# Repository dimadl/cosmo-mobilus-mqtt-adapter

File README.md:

# COSMO Mobilus shutters x Home Assistant (MQTT) Adapter
This repository provides all the necessary information—both software and hardware—to build your own adapter that connects COSMO Mobilus-controlled shutters to Home Assistant via MQTT.

The hardware setup is based on an actual COSMO Mobilus remote control and requires basic soldering skills to complete.

A high-level schematic of the end-to-end solution is shown in the diagram below.

## Motivation
There is no native support for COSMO protocol in Home Assistant.

## Features
- [x] Each shutter is automatically discovered by Home Assistant.
- [x] Position control is supported for each shutter, where 100 represents fully open and 0 fully closed.
- [x] Shutter positions are stored in memory to prevent re-synchronization after restarts.
- [x] The current position of the remote control unit is also saved in memory.

## Schematic

## Supported Device
- Mobilus COSMO HM
- Mobilus COSMO HM1
- Mobilus COSMO HM3+
- Mobilus COSMO G3+ Light (*)
- Mobilus COSMO WM (*)
- Mobilus COSMO L5 (*)
- Mobilus COSMO L1 (*)

(*) - These devices have not been tested; however, given that they use mechanical switches, this approach is expected to work with them as well.

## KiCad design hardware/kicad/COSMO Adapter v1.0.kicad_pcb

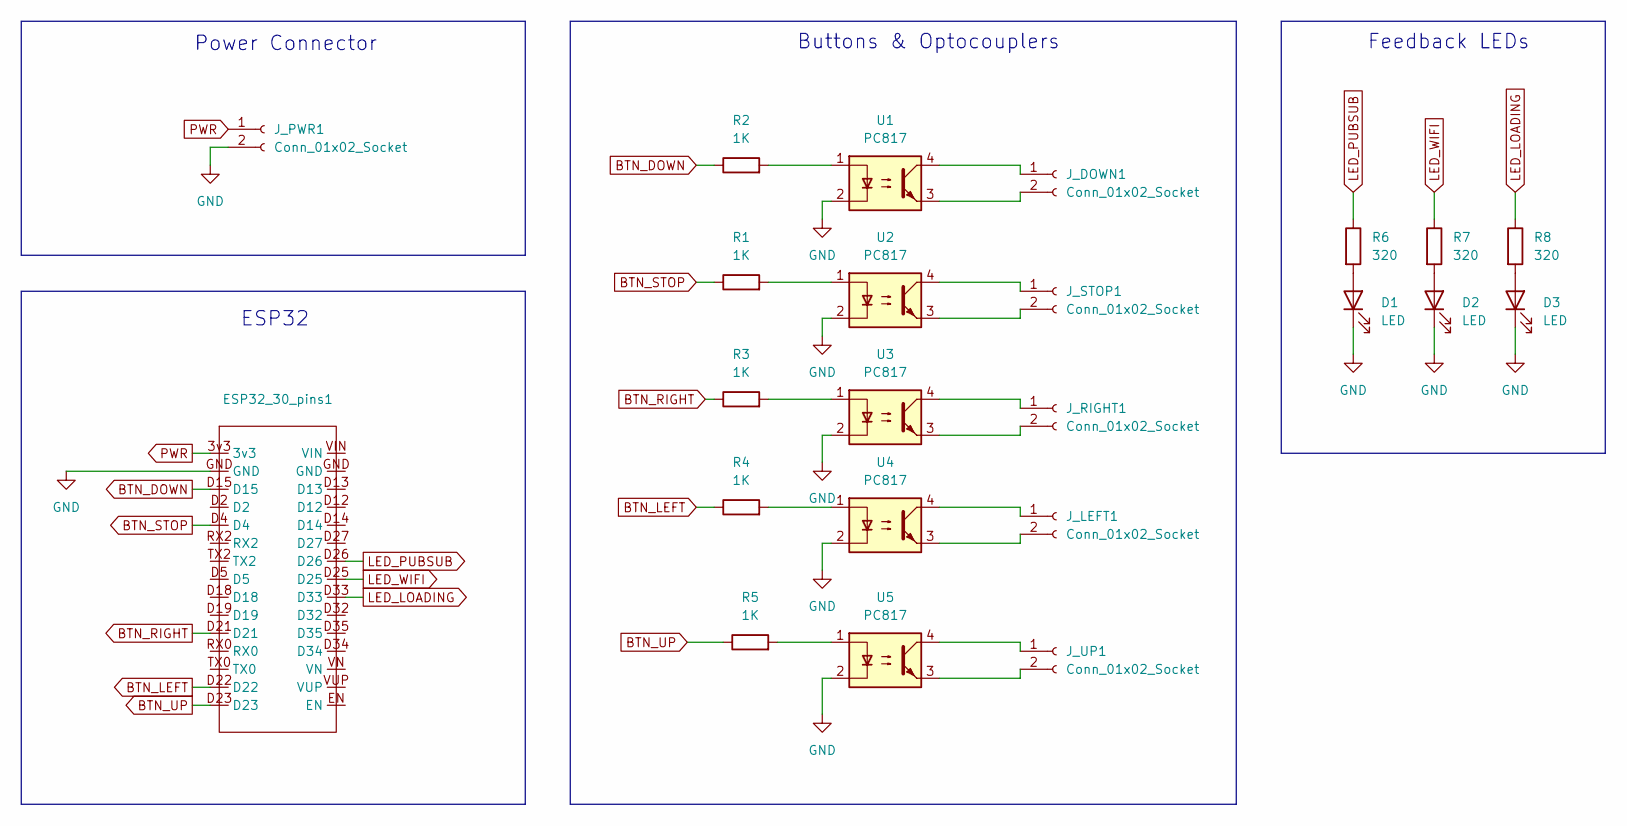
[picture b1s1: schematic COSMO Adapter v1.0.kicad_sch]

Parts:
D1, D2, D3: LED; LED_D3.0mm
ESP32_30_pins1: ESP_32_DevKit_30
J_DOWN1: Conn_01x02_Socket; PinHeader_1x02_P2.54mm_Vertical
J_LEFT1: Conn_01x02_Socket; PinHeader_1x02_P2.54mm_Vertical
J_PWR1: Conn_01x02_Socket; PinHeader_1x02_P2.54mm_Vertical
J_RIGHT1: Conn_01x02_Socket; PinHeader_1x02_P2.54mm_Vertical
J_STOP1: Conn_01x02_Socket; PinHeader_1x02_P2.54mm_Vertical
J_UP1: Conn_01x02_Socket; PinHeader_1x02_P2.54mm_Vertical
R1, R2, R3, R4, R5: 1K; R_Axial_DIN0207_L6.3mm_D2.5mm_P7.62mm_Horizontal
R6, R7, R8: 320; R_Axial_DIN0207_L6.3mm_D2.5mm_P7.62mm_Horizontal
U1, U2, U3, U4, U5: PC817; DIP-4_W7.62mm

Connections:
BTN_DOWN: ESP32_30_pins1.D15, R2.1
BTN_LEFT: ESP32_30_pins1.D22, R4.1
BTN_RIGHT: ESP32_30_pins1.D21, R3.1
BTN_STOP: ESP32_30_pins1.D4, R1.1
BTN_UP: ESP32_30_pins1.D23, R5.1
GND: D1.1 (K), D2.1 (K), D3.1 (K), ESP32_30_pins1.GND, J_PWR1.2, U1.2, U2.2, U3.2, U4.2, U5.2
LED_LOADING: ESP32_30_pins1.D33, R8.1
LED_PUBSUB: ESP32_30_pins1.D26, R6.1
LED_WIFI: ESP32_30_pins1.D25, R7.1
unnamed: D1.2 (A), R6.2
unnamed: D2.2 (A), R7.2
unnamed: D3.2 (A), R8.2
unnamed: J_DOWN1.1, U1.4
unnamed: J_DOWN1.2, U1.3
unnamed: J_LEFT1.1, U4.4
unnamed: J_LEFT1.2, U4.3
unnamed: J_RIGHT1.1, U3.4
unnamed: J_RIGHT1.2, U3.3
unnamed: J_STOP1.1, U2.4
unnamed: J_STOP1.2, U2.3
unnamed: J_UP1.1, U5.4
unnamed: J_UP1.2, U5.3
unnamed: R1.2, U2.1
unnamed: R2.2, U1.1
unnamed: R3.2, U3.1
unnamed: R4.2, U4.1
unnamed: R5.2, U5.1
PWR: ESP32_30_pins1.3v3, J_PWR1.1

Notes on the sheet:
ESP32
Feedback LEDs
Power Connector
Buttons & Optocouplers

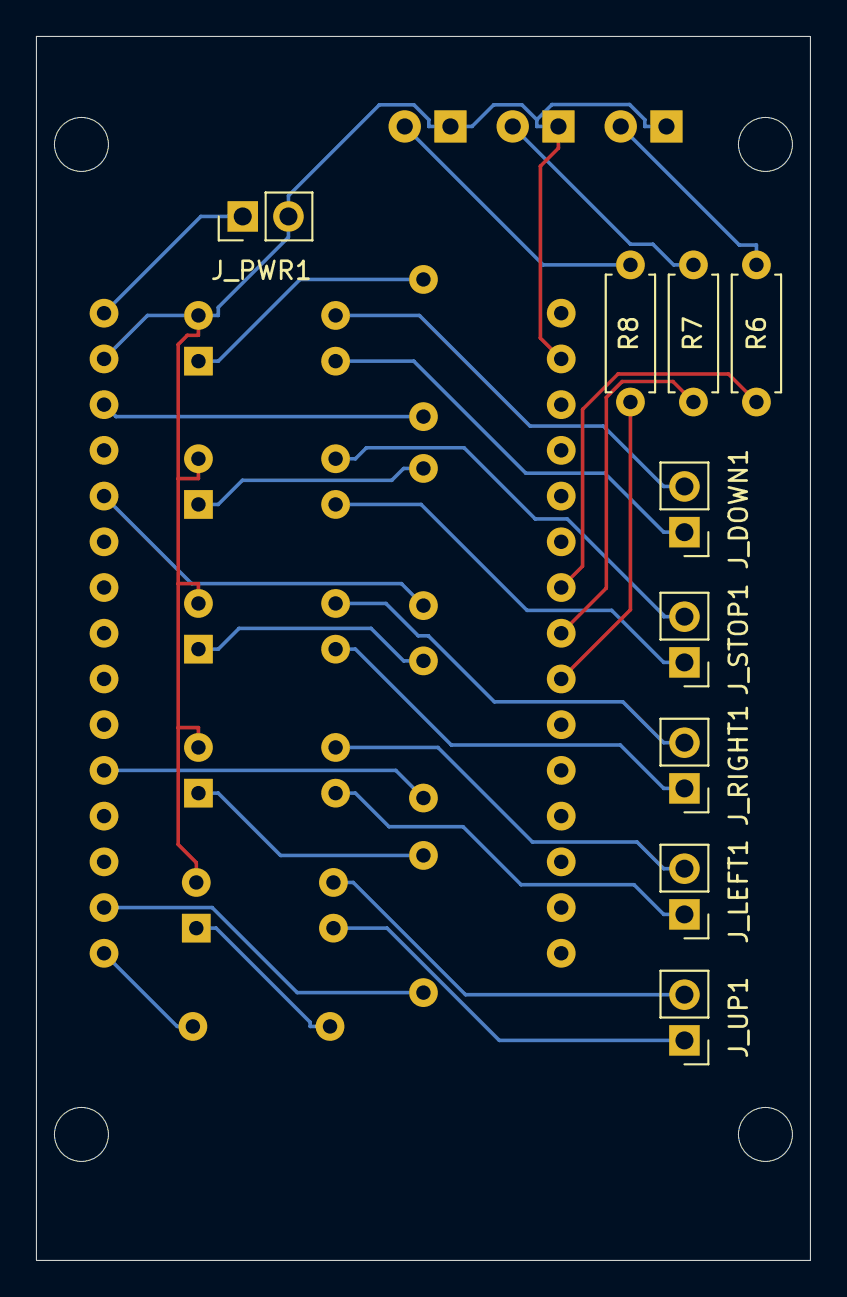
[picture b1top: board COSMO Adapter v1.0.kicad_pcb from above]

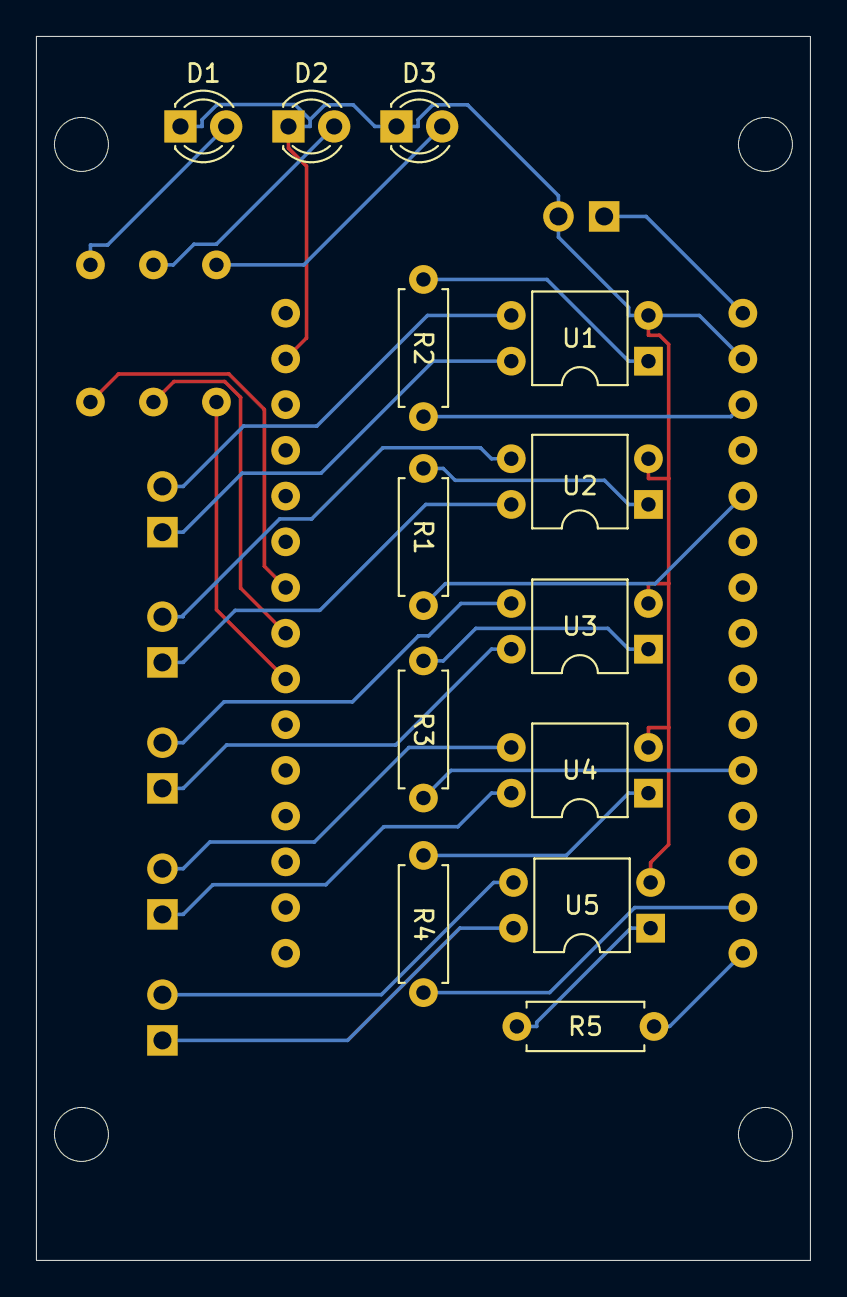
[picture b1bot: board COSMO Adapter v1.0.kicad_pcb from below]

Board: 2 copper layers, 43.0 x 68.0 mm, 23 parts (13 on the bottom side), 28 nets.

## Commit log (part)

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2025-08-03 Starts a project to integrate Cosmo Mobilus shutters with Home Assistant via MQTT protocol
2025-08-03 Adds MQTT support and integration with Home Assistant
    - Enables device discovery in Home Assistant
    - Implements simple callback for the command coming from the HA
    - Starts global refactorings to enable scaling up to several switches
2025-08-07 Adds new abstraction for the shutters
    - Implements HAMQTTShutter as a primary abstraction representing shutters
    - Unifies the way all shutter will send deiscovery message to Home Assistant via MQTT
2025-08-08 Iinitializes the controller abstraction
    - Adds a new abstraction HAMQTTShutterControl that will be controlling assigned shutters
    - Adds initialization of the registered shutters through the HAMQTTShutterControl
2025-08-09 Prepares the integration to receive commands from MQTT
    - Makes the shutter devices available for setting possition through automatios in Home Assistant
    - Every shutter subscribe to commands from Home Assistant (open, close, stop)
    - Pins initializtion for future optocouplers
2025-08-09 Implements a logic to set positions for the required shutter
    - Adds methods to manipulate the shutter (open, close, stop) based on the requested position
2025-08-09 Add abstraction for the hardware of Cosmo Mobilus HM control
2025-08-10 Fixed the issue with topics
2025-08-10 Added availability state sending
2025-08-10 Fixed the issue with positioning the current shutter on the control
2025-08-10 Refactors manipulation functions using pointers to the shutter
    - Repalces the array lookup with pointers to the shutter in the manupulation functions
2025-08-10 Adds "opened" and "closing" states to the shutter to report.
    - Home Assistant allows to have deterministic states for the shutter (opened, opening, closed, closing, stopped)
    - Adds report functions accordingly
2025-08-20 The first integration with real hardware.
    - Fixed few issues related to button press delays
    - Fixed an issue with moving counter on the hardware forward and backward (added delay to the button)
2025-08-20 Changed the size of EEPROM and moved current control position initisalization to the begin()
2025-08-21 Implements MQTT Client with fault tolerance and resilience
    - Implements rproxy for PubSubClient
    - Proxies "subscribe()" method with retry policies
    - Proxies "publish()" method with retru policies
2025-08-21 Refactors the proxy for MQTTClient
    - Moves MQTT broker initializtion to new proxy client
    - Moves callback inside of HAMQTTShutterControl
2025-08-24 Implements vfeedback on what's happenning inside
    - Adds a strategy that delegates feedback methods to LEDs.
    - Adds a onConnected callback for the MQTTClient. It can be usded to react re-connecrtion. The plan is to re-subscribe when a re-connection happened
2025-08-30 Adds README file with a description
2025-09-03 Replaces configuration with user inputs
    - Uses WifiManager to connect to wifi and as manager for MQTT configuration
    - Refactores main.cpp according to the latest changes
2025-09-08 Changes pin assignment for Stop button
2025-09-08 Implements "custom" handlers for CLOSE and OPEN commands
    - CLOSE and OPEN mean different things in the HA (please, check comments in the code). Voice control I'm using sends these commands as reactions to "Close 100%" and "Open 100%"
2025-09-08 Fixes an issue with not saved MQTT config
2025-09-08 Removes no longer needed wifi settings
2025-09-09 Implements dynamic initialization of shuttters.
    - Refactros the location of shutter-related classes;
    - Adds loading of shutter configuration from JSON string
    In the future, JSON string will allow a quick transformation to a WEB page with configuration fields.
2025-09-13 Adds back-pressure mechanism for messages received from different topic
    - Adds queue between PubSubCclient and a message handler
    - handles messages from queue in a isolated task attached to the second core of processor while the first core processes main sequence
2025-09-13 Adds reboot possibility from HA
    - Listenes for command "reboot" in the dedicated topic. When the message arrives it triggeres reboot mechanism
2025-12-16 Optimizes the way shutters fully open and fully close
    The code removes unneeded delay between shutters that can be fully closed without pressing the stop button
2025-12-16 Adds Kicad project (schematic, PCB and Gerber files
2025-12-16 Adds schematic PNG to README.md file
2025-12-28 Adds a health check prosessor based on the ping messages sent from the external system over MQTT.
    - THe entire helath check mechanism relies on the ping messages received from Home Assistant (in my case) over MQTT in the dedicated topic
    - Refactores the previous attempt of the health check and device reboot.
2025-12-29 CA-5. Adds ElegantOTA library
2025-12-29 CA-5. Adds PlatformIO build status label to the README file
2025-12-29 CA-5. Adds Github Action to build the firmware
2025-12-29 CA-5. Adds ElegantOTA for the Over The Air functionality
    - ElegantOTA connected in the platformio.ini file
    - Adds version to the name of built firmware bin file
